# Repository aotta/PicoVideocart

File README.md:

# PicoVideocart

changelog: v.1.1 added with new Adafruit USB stack

Flash cart for SABA Videoplay - porting of 3DMaze PicoVideocart

This is a forked version of https://github.com/ZX-80/PicoVideocart (see original project for details) for using a cheaper and simpler pcb based on pico "Purple" clone and using its 16mb flash for storing games instead of the original SDCard

Since now it was only tested on SABA Videoplay (PAL), but it should work in Fairchild Channel-F (NTSC) too.

Thanks to my friend Dave, here's some more info and the label for the shell:
https://www.nightfallcrew.com/05/09/2024/flash-multicart-for-saba-videoplay-fairchild-channel-f/

**WARNING!** "purple" Pico has not the same pinout of original Raspberry "green" ones, you MUST use the clone or you may damage your hardware.

Kicad project and gerbers files for the pcb are in the PCB folder, you need only a diode and a push buttons for resetting the cart if needed or want restart. 
Add you pico clone, and flash the firmware ".uf2" in the Pico by connecting it while pressing button on Pico and drop it in the opened windows on PC.

in V.1.0, "Bin" files should be added in flash using Arduino IDE plugin ( https://github.com/earlephilhower/arduino-littlefs-upload )
be sure to put boot.bin with other games, it's the menu selector.

**NOTE: V.1.1 use now Adafruit stack USB and you can upload bin files by connecting the card to a PC via usb cable and copying them on the flash folder. First time flash folder need to be formatted as FAT disk.
Now the multicart check at boot if it's inserted in console, if you get flashing led at boot, reset Picovideocart or powercycle the console until you get a steady flash led.

More info on AtariAge forum: https://forums.atariage.com/topic/274416-the-official-channel-f-thread/page/56/

Even if the diode should protect your console, **DO NOT CONNECT PICO WHILE INSERTED IN A POWERED ON CONSOLE!**

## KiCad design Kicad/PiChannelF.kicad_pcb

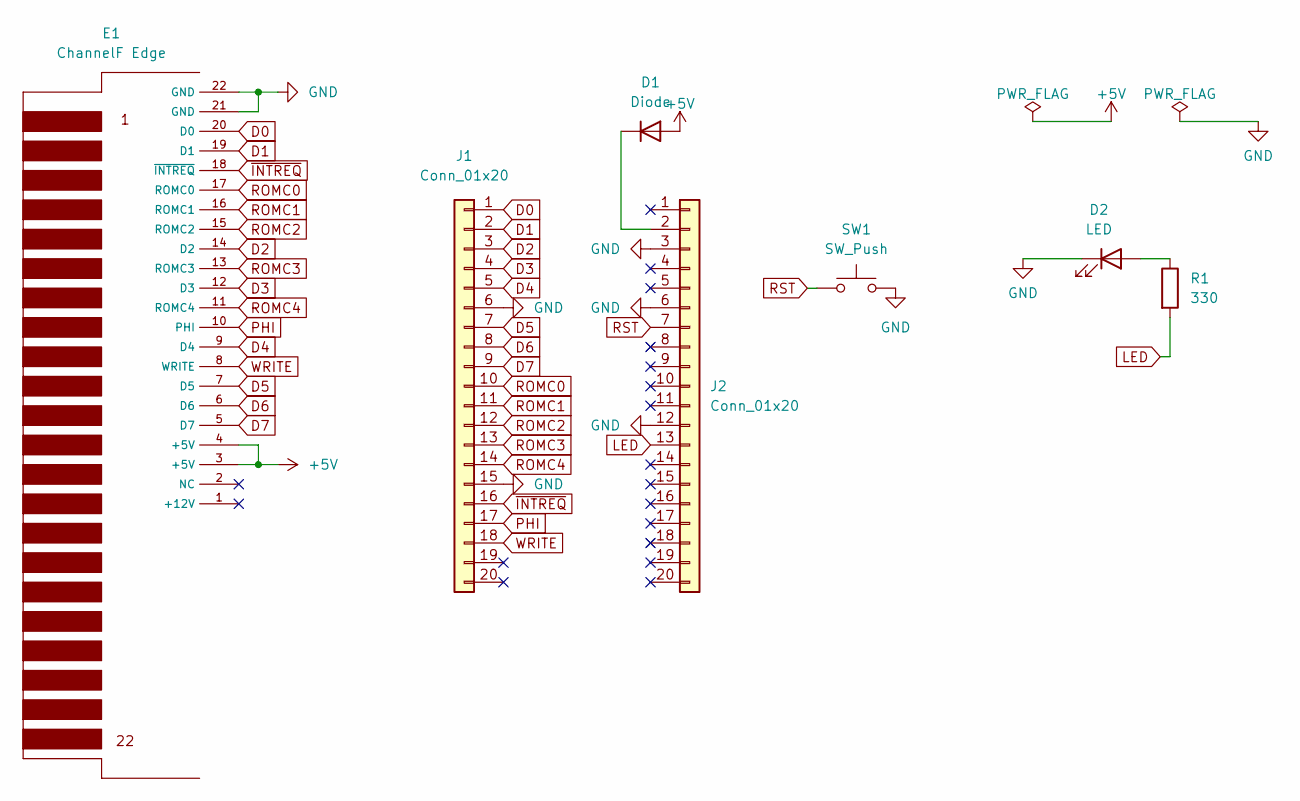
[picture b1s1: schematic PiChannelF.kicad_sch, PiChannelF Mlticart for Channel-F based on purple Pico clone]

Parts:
D1: Diode; D_DO-35_SOD27_P7.62mm_Horizontal
D2: LED; LED_D3.0mm
E1: ChannelF Edge; ChannelF_EDGE
J1, J2: Conn_01x20; PinSocket_1x20_P2.54mm_Vertical
R1: 330; R_Axial_DIN0207_L6.3mm_D2.5mm_P7.62mm_Horizontal
SW1: SW_Push; SW_Tactile_SPST_Angled_PTS645Vx58-2LFS

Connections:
+5V: D1.2 (A), E1.3 (+5V), E1.4 (+5V)
D0: E1.20 (D0), J1.1
D1: E1.19 (D1), J1.2
D2: E1.14 (D2), J1.3
D3: E1.12 (D3), J1.4
D4: E1.9 (D4), J1.5
D5: E1.7 (D5), J1.7
D6: E1.6 (D6), J1.8
D7: E1.5 (D7), J1.9
GND: D2.1 (K), E1.21 (GND), E1.22 (GND), J1.6, J1.15, J2.3, J2.6, J2.12, SW1.2
LED: J2.13, R1.2
unnamed: D1.1 (K), J2.2
unnamed: D2.2 (A), R1.1
PHI: E1.10 (PHI), J1.17
ROMC0: E1.17 (ROMC0), J1.10
ROMC1: E1.16 (ROMC1), J1.11
ROMC2: E1.15 (ROMC2), J1.12
ROMC3: E1.13 (ROMC3), J1.13
ROMC4: E1.11 (ROMC4), J1.14
RST: J2.7, SW1.1
WRITE: E1.8 (WRITE), J1.18
~INTREQ: E1.18 (~INTREQ), J1.16

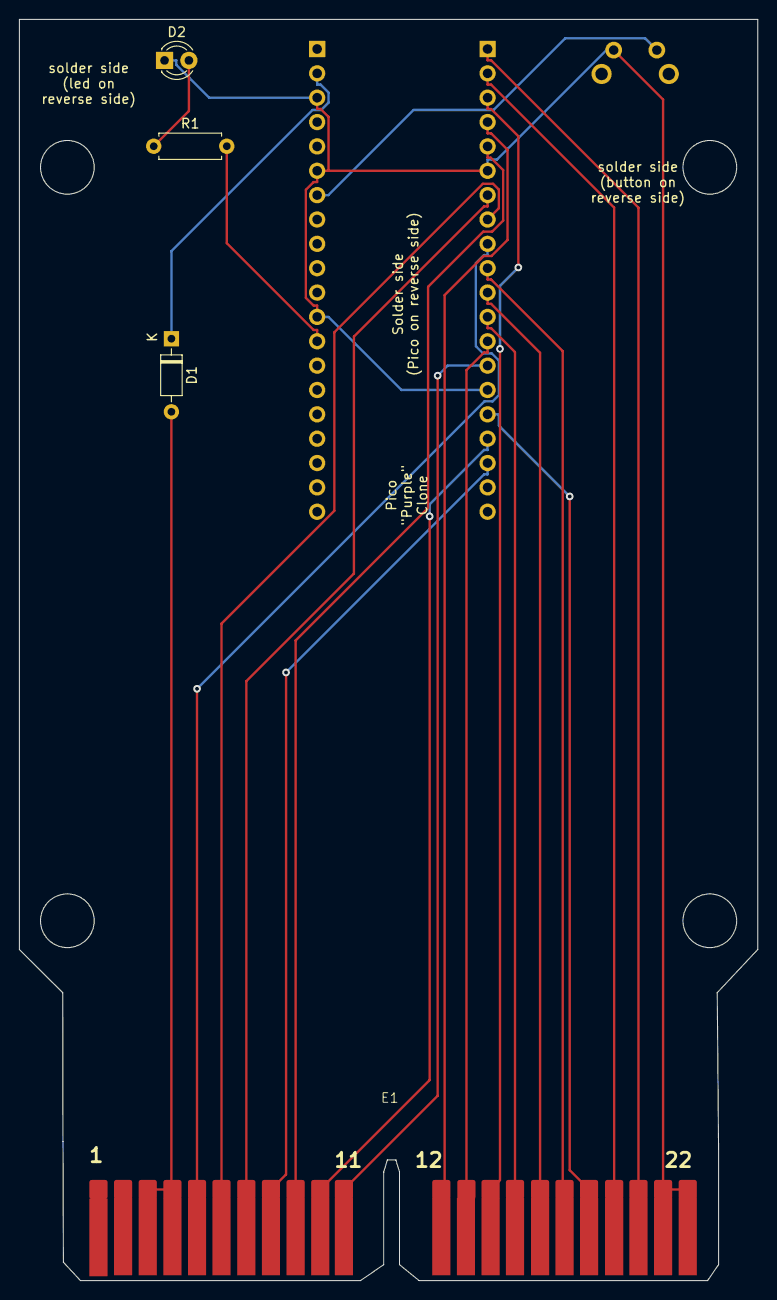
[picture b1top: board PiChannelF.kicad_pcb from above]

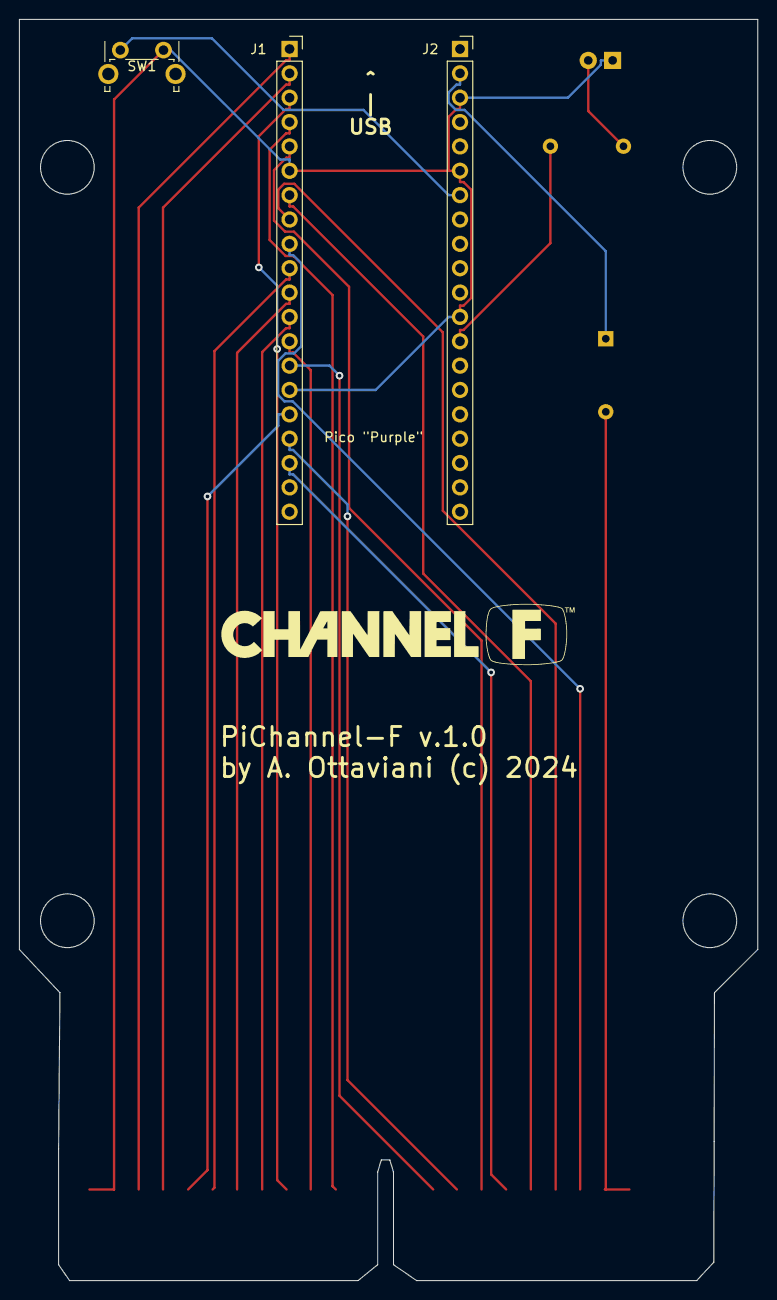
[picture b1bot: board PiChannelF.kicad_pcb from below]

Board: 2 copper layers, 77.0 x 131.5 mm, 7 parts (3 on the bottom side), 22 nets.

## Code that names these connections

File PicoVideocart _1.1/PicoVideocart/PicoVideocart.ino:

/* \file PicoVideocart.ino
 */
// V.1.1  moved from LittleFS to Adafruit USB Stack

#include "loader.hpp"
#include "error.hpp"
#include "romc.hpp"
#include "pico/stdlib.h"
#include "hardware/adc.h"
#include "hardware/flash.h"
#include "hardware/vreg.h"
#include "hardware/structs/bus_ctrl.h"
#include "SdFat_Adafruit_Fork.h"
#include "Adafruit_SPIFlash.h"
#include "Adafruit_TinyUSB.h"

Adafruit_FlashTransport_RP2040 flashTransport;
Adafruit_SPIFlash flash(&flashTransport);

FatVolume fatfs;
File32 root;
File32 file;
File32 romFile;

Adafruit_USBD_MSC usb_msc;
bool fs_formatted;
bool fs_changed = false;

// Pin definitions
#define D0_PIN     0
#define D1_PIN     1
#define D2_PIN     2
#define D3_PIN     3
#define D4_PIN     4
#define D5_PIN     5
#define D6_PIN     6
#define D7_PIN     7
#define ROMC0_PIN  8
#define ROMC1_PIN  9
#define ROMC2_PIN 10
#define ROMC3_PIN 11
#define ROMC4_PIN 12
#define INTREQ_PIN 13
#define PHI_PIN    14
#define WRITE_PIN  15

#define DATA_PIN_MASK   0x000000FFL
#define SET_DATA_MODE_OUT   gpio_set_dir_out_masked(DATA_PIN_MASK)
#define SET_DATA_MODE_IN    gpio_set_dir_in_masked(DATA_PIN_MASK)

// Callbacks USB MSC
int32_t msc_read_cb(uint32_t lba, void* buffer, uint32_t bufsize) {
  return flash.readBlocks(lba, (uint8_t*)buffer, bufsize / 512) ? bufsize : -1;
}

int32_t msc_write_cb(uint32_t lba, uint8_t* buffer, uint32_t bufsize) {
  return flash.writeBlocks(lba, buffer, bufsize / 512) ? bufsize : -1;
}

void msc_flush_cb(void) {
  flash.syncBlocks();
  fatfs.cacheClear();
  fs_changed = true;
}


void setup1() {
  bus_ctrl_hw->priority = BUSCTRL_BUS_PRIORITY_PROC1_BITS;
  
  for (int i = 0; i < 8; i++) {
    gpio_set_function(D0_PIN + i, GPIO_FUNC_SIO);
  }
  for (int i = 0; i < 5; i++) {
    gpio_set_function(ROMC0_PIN + i, GPIO_FUNC_SIO);
  }
  
  gpio_init(WRITE_PIN);
  gpio_set_dir(WRITE_PIN, GPIO_IN);
  gpio_init(PHI_PIN);
  gpio_set_dir(PHI_PIN, GPIO_IN);
  gpio_init(INTREQ_PIN);
  gpio_set_dir(INTREQ_PIN, GPIO_OUT);
  gpio_put(INTREQ_PIN, true);
  gpio_init(LED_BUILTIN);
  gpio_set_dir(LED_BUILTIN, GPIO_OUT);
  gpio_put(LED_BUILTIN, true);
}

void __not_in_flash_func(loop1)() {
  for (;;) {
    while(gpio_get(WRITE_PIN));
    SET_DATA_MODE_IN;
    while(gpio_get(WRITE_PIN) == 0);
    SET_DATA_MODE_IN;
    dbus = read_dbus();
    romc = read_romc();
    execute_romc();
  }
}

void setup() {
  
  
  // Verifica se siamo collegati alla console
  bool carton = false;
  int t = 100;
  
  while (gpio_get(PHI_PIN) == 0 && to_ms_since_boot(get_absolute_time()) < 2000) {
    if (to_ms_since_boot(get_absolute_time()) > t) {
      t += 100;
    }
    sleep_ms(1);
  }
  
 if (gpio_get(PHI_PIN) == 1) {
    carton = true;  
 }
  
  // Inizializza flash
  flash.begin();
  
  // Configura USB MSC
  usb_msc.setID("PicoVideocart", "External Flash", "1.0");
  usb_msc.setReadWriteCallback(msc_read_cb, msc_write_cb, msc_flush_cb);
  usb_msc.setCapacity(flash.size() / 512, 512);
  usb_msc.setUnitReady(true);
  usb_msc.begin();
  
  if (TinyUSBDevice.mounted()) {
    TinyUSBDevice.detach();
    sleep_ms(10);
    TinyUSBDevice.attach();
    sleep_ms(10);
  }
  
  // Monta filesystem
  fs_formatted = fatfs.begin(&flash);
  
  if (!carton) {
    // Modalità PC
    usb_msc.setUnitReady(true);
    while (1) {
      blink_code(1);
    }
  }
  
  // === MODALITÀ CONSOLE ===
  usb_msc.setUnitReady(false);
  
  
  // === SCANSIONE FILE ===
  uint16_t file_counter = 0;
  
  if (root.open("/", O_RDONLY)) {
    while (file_counter < FOLDER_LIMIT) {
      if (!file.openNext(&root, O_RDONLY)) break;
      
      if (!file.isDir()) {
        char filename[256];
        file.getName(filename, sizeof(filename));
        
        // Verifica estensione .bin o .chf
        int len = strlen(filename);
        bool is_valid = false;
        
        if (len > 4) {
          if (strcmp(filename + len - 4, ".bin") == 0) {
            is_valid = true;
          } else if (strcmp(filename + len - 4, ".chf") == 0) {
            is_valid = true;
          }
        }
        
        if (is_valid) {
          file_data[file_counter].isFile = true;
          file_data[file_counter].title[0] = ' ';
          
          // Copia il nome senza estensione
          char display_name[32];
          strncpy(display_name, filename, 31);
          if (len > 4 && strcmp(filename + len - 4, ".bin") == 0) {
            display_name[len - 4] = '\0';
          }
          strncpy((char*)file_data[file_counter].title + 1, display_name, 30);
          file_data[file_counter].title[31] = '\0';
          
          file_counter++;
        }
      }
      file.close();
    }
    root.close();
  }
  
  DIR_LIMIT = file_counter;
  
  // === SEGNALA QUANTI FILE SONO STATI TROVATI ===
  // Lampeggia il numero di file trovati (es: 3 file = 3 lampeggi)
  if (DIR_LIMIT == 0) {
    // Nessun file trovato: lampeggio rapido continuo
    blink_code(BLINK::NO_VALID_FILES, 5);
  }
  
  // Scrivi il primo titolo nella RAM
  if (DIR_LIMIT > 0) {
    strncpy((char*)program_rom + SRAM_START_ADDR + 2, 
            file_data[0].title, 30);
  } else {
    const char* no_data = "No Data";
    for (int i = 0; i < 8; i++) {
      program_rom[SRAM_START_ADDR + 2 + i] = no_data[i];
    }
  }
  //File32 romFile;
  // === CARICA BOOT.BIN ===
  romFile = fatfs.open("/boot.bin", O_RDONLY);
  if (!romFile) {
    romFile = fatfs.open("/boot_old.bin", O_RDONLY);
  }
  
  // Carica il boot (lampeggio durante il caricamento)
  load_game(romFile);
  
  // Overclock
  vreg_set_voltage(VREG_VOLTAGE_1_30);
  sleep_ms(1);
  if (!set_sys_clock_khz(360000, false)) {
    blink_code(BLINK::OVERCLOCK_FAILED, 2);
    set_sys_clock_khz(300000, false);
  }
  
  // LED acceso fisso = tutto OK
  gpio_put(LED_BUILTIN, true);
}

void loop() {
  sleep_ms(100);
  
  if (load_new_game_trigger) {
    load_new_game_trigger = false;
    
    // Lampeggio rapido durante il caricamento
    gpio_put(LED_BUILTIN, false);
    
    while (pc0 >= 0x800) {
      sleep_ms(1);
    }
    
    uint16_t file_index = static_cast<Launcher*>(IOPorts[0xFF])->file_index;
    
    if (file_index < DIR_LIMIT) {
      char filename[32];
      strcpy(filename, file_data[file_index].title);
      filename[0] = '/';
      // Ricostruisci il nome completo con estensione
      strcat(filename, ".bin");
      //File32 romFile;
      romFile = fatfs.open(filename, O_RDONLY);
      if (romFile) {
        load_game(romFile);
        
        if (!set_sys_clock_khz(400000, false)) {
          set_sys_clock_khz(300000, false);
        }
      }
    }
    
    gpio_put(LED_BUILTIN, true);
  }
}

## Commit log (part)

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2024-08-11 Add files via upload
    little shift and enlarge of holes for screw in pcb
2024-08-13 Add files via upload
    added "thinking" led in Schach Saba cart
2024-09-05 Update README.md
    added link for firmware and shell label
2026-04-25 V.1.1 with USB file adding from pc
2026-04-25 New version 1.1
2026-04-26 Update README.md
    added v.1.1 changelog

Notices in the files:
Kicad/PiChannelF.kicad_pcb:
by A. Ottaviani (c) 2024
